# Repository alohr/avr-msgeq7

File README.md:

# MSGEQ7 based audio spectrum analyzer

This is a audio spectrum analyzer based on the msgeq7 using an lm3915 as the display driver and an attiny2313 for timing.

## Sandwiched boards in a "sick of beige" case

[Build instructions](kit-r1.md)

## Schematic

## Breadboard

## "Stereo" on a breadboard

Use two msgeq7 and lm3915's to handle the two audio channels independent from each other. One attiny2313 drives both channnels.

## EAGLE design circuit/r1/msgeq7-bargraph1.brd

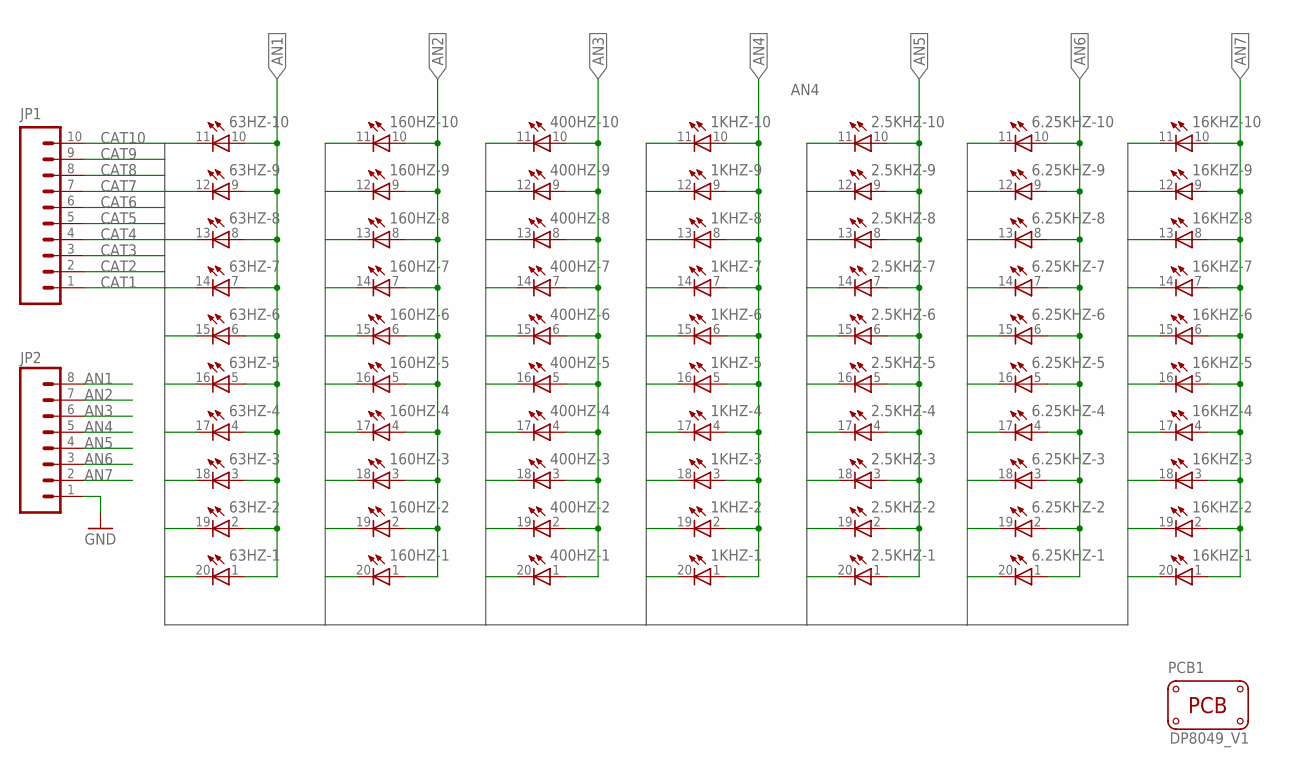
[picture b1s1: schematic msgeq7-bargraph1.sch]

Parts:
1KHZ, 2.5KHZ, 6.25KHZ, 16KHZ, 63HZ, 160HZ, 400HZ: LB10
JP1: M10"; 1X10
JP2: M081X08; 1X08
PCB1: PCB_DP_RECTANGLE-80X49; DP8049_V1

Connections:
AN1: 63HZ.1 (A), 63HZ.2 (A), 63HZ.3 (A), 63HZ.4 (A), 63HZ.5 (A), 63HZ.6 (A), 63HZ.7 (A), 63HZ.8 (A), 63HZ.9 (A), 63HZ.10 (A), JP2.8
AN2: 160HZ.1 (A), 160HZ.2 (A), 160HZ.3 (A), 160HZ.4 (A), 160HZ.5 (A), 160HZ.6 (A), 160HZ.7 (A), 160HZ.8 (A), 160HZ.9 (A), 160HZ.10 (A), JP2.7
AN3: 400HZ.1 (A), 400HZ.2 (A), 400HZ.3 (A), 400HZ.4 (A), 400HZ.5 (A), 400HZ.6 (A), 400HZ.7 (A), 400HZ.8 (A), 400HZ.9 (A), 400HZ.10 (A), JP2.6
AN4: 1KHZ.1 (A), 1KHZ.2 (A), 1KHZ.3 (A), 1KHZ.4 (A), 1KHZ.5 (A), 1KHZ.6 (A), 1KHZ.7 (A), 1KHZ.8 (A), 1KHZ.9 (A), 1KHZ.10 (A), JP2.5
AN5: 2.5KHZ.1 (A), 2.5KHZ.2 (A), 2.5KHZ.3 (A), 2.5KHZ.4 (A), 2.5KHZ.5 (A), 2.5KHZ.6 (A), 2.5KHZ.7 (A), 2.5KHZ.8 (A), 2.5KHZ.9 (A), 2.5KHZ.10 (A), JP2.4
AN6: 6.25KHZ.1 (A), 6.25KHZ.2 (A), 6.25KHZ.3 (A), 6.25KHZ.4 (A), 6.25KHZ.5 (A), 6.25KHZ.6 (A), 6.25KHZ.7 (A), 6.25KHZ.8 (A), 6.25KHZ.9 (A), 6.25KHZ.10 (A), JP2.3
AN7: 16KHZ.1 (A), 16KHZ.2 (A), 16KHZ.3 (A), 16KHZ.4 (A), 16KHZ.5 (A), 16KHZ.6 (A), 16KHZ.7 (A), 16KHZ.8 (A), 16KHZ.9 (A), 16KHZ.10 (A), JP2.2
CAT1: 1KHZ.20 (C), 2.5KHZ.20 (C), 6.25KHZ.20 (C), 16KHZ.20 (C), 63HZ.20 (C), 160HZ.20 (C), 400HZ.20 (C), JP1.1
CAT2: 1KHZ.19 (C), 2.5KHZ.19 (C), 6.25KHZ.19 (C), 16KHZ.19 (C), 63HZ.19 (C), 160HZ.19 (C), 400HZ.19 (C), JP1.2
CAT3: 1KHZ.18 (C), 2.5KHZ.18 (C), 6.25KHZ.18 (C), 16KHZ.18 (C), 63HZ.18 (C), 160HZ.18 (C), 400HZ.18 (C), JP1.3
CAT4: 1KHZ.17 (C), 2.5KHZ.17 (C), 6.25KHZ.17 (C), 16KHZ.17 (C), 63HZ.17 (C), 160HZ.17 (C), 400HZ.17 (C), JP1.4
CAT5: 1KHZ.16 (C), 2.5KHZ.16 (C), 6.25KHZ.16 (C), 16KHZ.16 (C), 63HZ.16 (C), 160HZ.16 (C), 400HZ.16 (C), JP1.5
CAT6: 1KHZ.15 (C), 2.5KHZ.15 (C), 6.25KHZ.15 (C), 16KHZ.15 (C), 63HZ.15 (C), 160HZ.15 (C), 400HZ.15 (C), JP1.6
CAT7: 1KHZ.14 (C), 2.5KHZ.14 (C), 6.25KHZ.14 (C), 16KHZ.14 (C), 63HZ.14 (C), 160HZ.14 (C), 400HZ.14 (C), JP1.7
CAT8: 1KHZ.13 (C), 2.5KHZ.13 (C), 6.25KHZ.13 (C), 16KHZ.13 (C), 63HZ.13 (C), 160HZ.13 (C), 400HZ.13 (C), JP1.8
CAT9: 1KHZ.12 (C), 2.5KHZ.12 (C), 6.25KHZ.12 (C), 16KHZ.12 (C), 63HZ.12 (C), 160HZ.12 (C), 400HZ.12 (C), JP1.9
CAT10: 1KHZ.11 (C), 2.5KHZ.11 (C), 6.25KHZ.11 (C), 16KHZ.11 (C), 63HZ.11 (C), 160HZ.11 (C), 400HZ.11 (C), JP1.10
GND: JP2.1

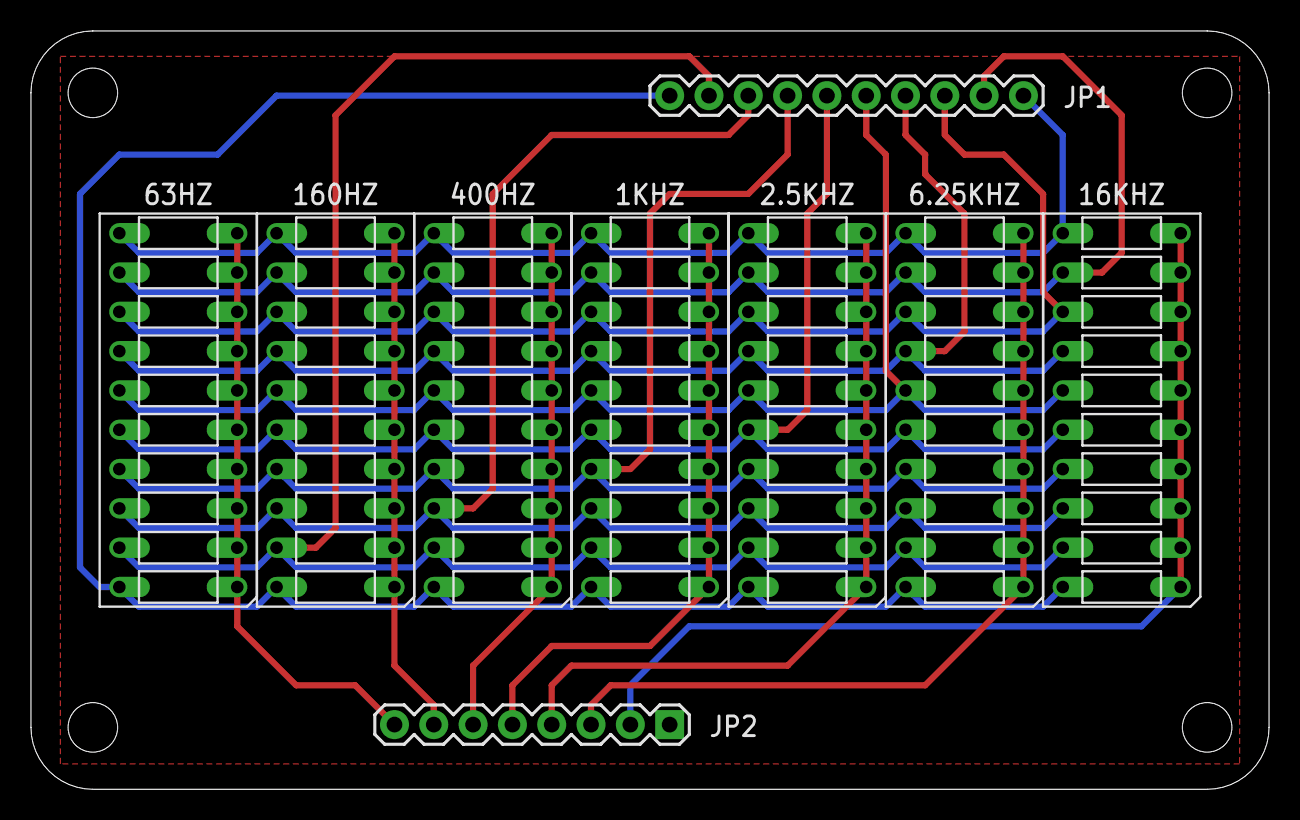
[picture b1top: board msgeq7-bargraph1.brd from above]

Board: 2 copper layers, 80.0 x 49.0 mm, 10 parts (0 on the bottom side), 17 nets.

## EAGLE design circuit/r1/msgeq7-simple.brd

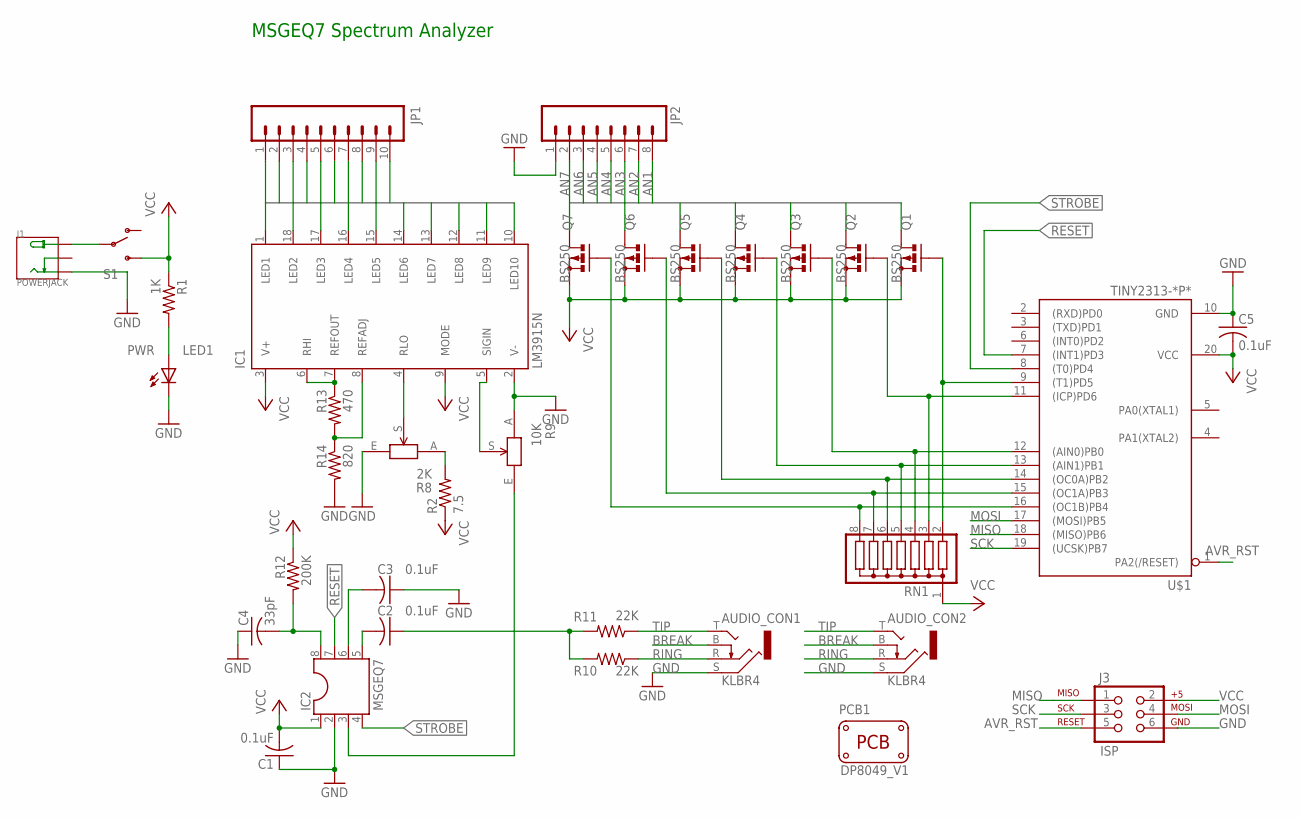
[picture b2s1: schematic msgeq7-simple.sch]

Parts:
AUDIO_CON1, AUDIO_CON2: KLBR4
C1, C2, C3, C5: 0.1uF; C025-025X050
C4: 33pF; C025-025X050
IC1: LM3915N; DIL18
IC2: MSGEQ7; DIL08
J1: POWERJACK; PW-3P-2.1
J3: ISP; 2X3
JP1: M10"; 1X10
JP2: M081X08; 1X08
LED1: PWR; LED3MM
PCB1: PCB_DP_RECTANGLE-80X49; DP8049_V1
Q1, Q2, Q3, Q4, Q5, Q6, Q7: BS250; TO92-E-LINE
R1: 1K; AXIAL-0.4
R2: 7.5; AXIAL-0.4
R8: 2K; 3352T
R9: 10K; 3352T
R10, R11: 22K; AXIAL-0.4
R12: 200K; AXIAL-0.4
R13: 470; AXIAL-0.4
R14: 820; AXIAL-0.4
RN1: G07R; SIL8
S1: SWITCH-SPDTPTH; SWITCH-SPDT
U$1: TINY2313-*P*; DIL20

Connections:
AN1: JP2.8, Q1.D
AN2: JP2.7, Q2.D
AN3: JP2.6, Q3.D
AN4: JP2.5, Q4.D
AN5: JP2.4, Q5.D
AN6: JP2.3, Q6.D
AN7: JP2.2, Q7.D
AVR_RST: J3.5, U$1.1 (PA2(/RESET))
BREAK: AUDIO_CON1.B, AUDIO_CON2.B
CAT1: IC1.1 (LED1), JP1.1
CAT2: IC1.18 (LED2), JP1.2
CAT3: IC1.17 (LED3), JP1.3
CAT4: IC1.16 (LED4), JP1.4
CAT5: IC1.15 (LED5), JP1.5
CAT6: IC1.14 (LED6), JP1.6
CAT7: IC1.13 (LED7), JP1.7
CAT8: IC1.12 (LED8), JP1.8
CAT9: IC1.11 (LED9), JP1.9
CAT10: IC1.10 (LED10), JP1.10
GND: AUDIO_CON1.S, AUDIO_CON2.S, C1.1, C3.1, C4.1, C5.1, IC1.2 (V-), IC2.2, J1.-1 (-), J3.6, JP2.1, LED1.K (C), R8.E, R9.A, R14.P$2 (2), U$1.10 (GND)
MISO: J3.1, U$1.18 ((MISO)PB6)
MOSI: J3.4, U$1.17 ((MOSI)PB5)
unnamed: Q7.G, RN1.8, U$1.16 ((OC1B)PB4)
unnamed: Q6.G, RN1.7, U$1.15 ((OC1A)PB3)
unnamed: Q5.G, RN1.6, U$1.14 ((OC0A)PB2)
unnamed: Q4.G, RN1.5, U$1.13 ((AIN1)PB1)
unnamed: Q3.G, RN1.4, U$1.12 ((AIN0)PB0)
unnamed: Q2.G, RN1.3, U$1.11 ((ICP)PD6)
unnamed: Q1.G, RN1.2, U$1.9 ((T1)PD5)
unnamed: IC1.4 (RLO), R8.S
unnamed: IC1.5 (SIGIN), R9.S
unnamed: C2.2, IC2.5
unnamed: IC2.3, R9.E
unnamed: J1.+, S1.2
unnamed: C2.1, R10.P$2 (2), R11.P$2 (2)
unnamed: C3.2, IC2.6
unnamed: C4.2, IC2.8, R12.P$2 (2)
unnamed: IC1.6 (RHI), IC1.7 (REFOUT), R13.P$1 (1)
unnamed: IC1.8 (REFADJ), R13.P$2 (2), R14.P$1 (1)
unnamed: LED1.A, R1.P$2 (2)
unnamed: R2.P$2 (2), R8.A
RESET: IC2.7, U$1.7 ((INT1)PD3)
RING: AUDIO_CON1.R, AUDIO_CON2.R, R10.P$1 (1)
SCK: J3.3, U$1.19 ((UCSK)PB7)
STROBE: IC2.4, U$1.8 ((T0)PD4)
TIP: AUDIO_CON1.T, AUDIO_CON2.T, R11.P$1 (1)
VCC: C1.2, C5.2, IC1.3 (V+), IC1.9 (MODE), IC2.1, J3.2, Q1.S, Q2.S, Q3.S, Q4.S, Q5.S, Q6.S, Q7.S, R1.P$1 (1), R2.P$1 (1), R12.P$1 (1), RN1.1, S1.3 (S), U$1.20 (VCC)

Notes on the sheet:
MSGEQ7 Spectrum Analyzer

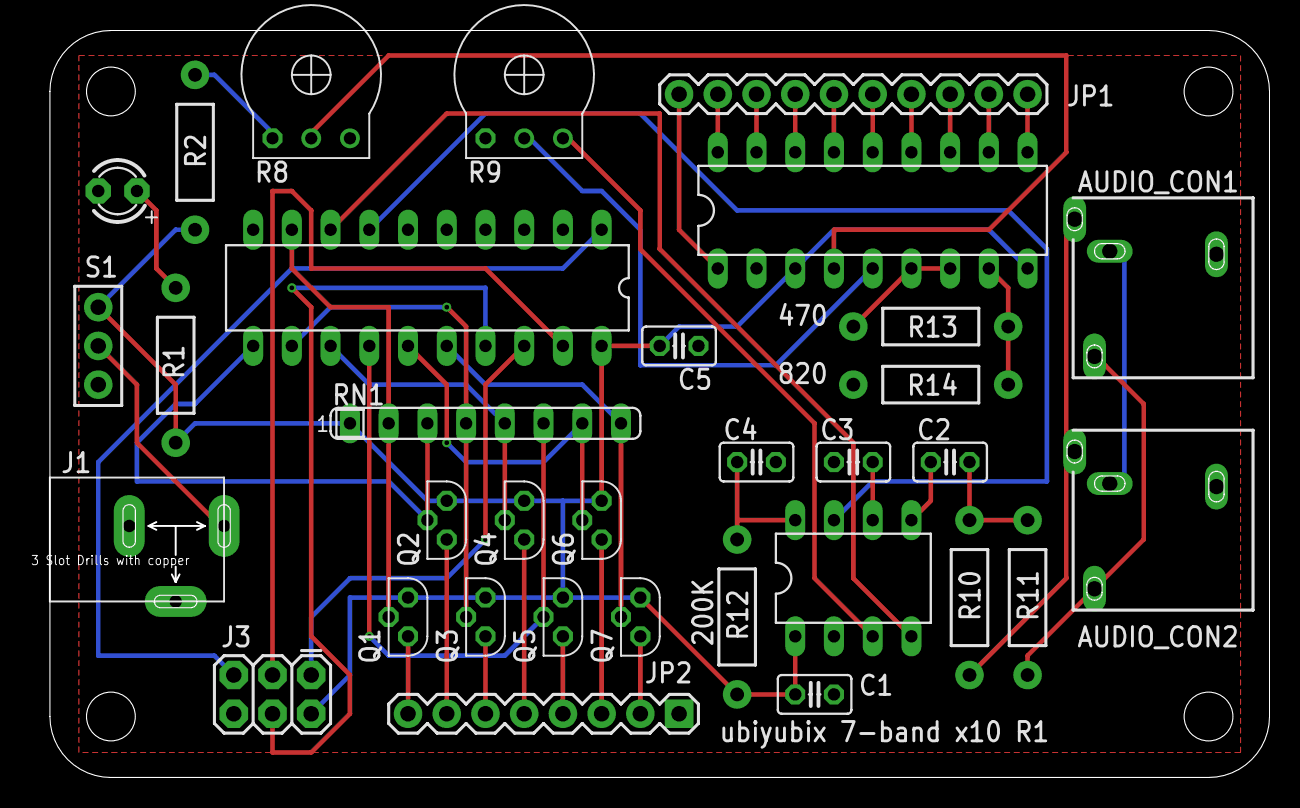
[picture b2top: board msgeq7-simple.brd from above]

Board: 2 copper layers, 81.1 x 48.9 mm, 34 parts (0 on the bottom side), 47 nets.

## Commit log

2015-06-28 added firmware
2015-06-28 added simple circuit
2015-06-28 added lm3915 current calculator
2015-07-12 added stereo on a breadboard image
2015-07-12 try centering images
2015-07-12 center schematic
2015-07-12 removed old .png
2015-07-12 fixed location of R12
2015-07-12 new schematic image
2015-07-12 added mono image
2015-07-12 new stereo image
2015-07-12 fixed image location
2015-07-12 fixed image location again (sigh)
2015-08-28 ordered r1 of circuit boards from seeed
2015-11-09 reverse order
2015-11-09 step1
2015-11-09 added kit build instructions
2015-11-09 larger
2015-11-09 step1a
2015-11-09 step1a image
2015-11-09 step2
2015-11-09 next steps
2015-11-09 step 7
2015-11-15 added finished kit image
2015-11-17 added fuse settings for different devices
2015-11-19 added arduino
2015-11-28 fixed attiny85 8 mhz
2015-11-29 fixed link to schematic
2015-11-29 fixed link to schematic (next try)
2015-11-29 removed duplicated image
2015-11-29 link to build instructions

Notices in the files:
parts and their libraries:
SparkFun-Passives: Licensing: CC v3.0 Share-Alike You are welcome to use this library for commercial purposes.
